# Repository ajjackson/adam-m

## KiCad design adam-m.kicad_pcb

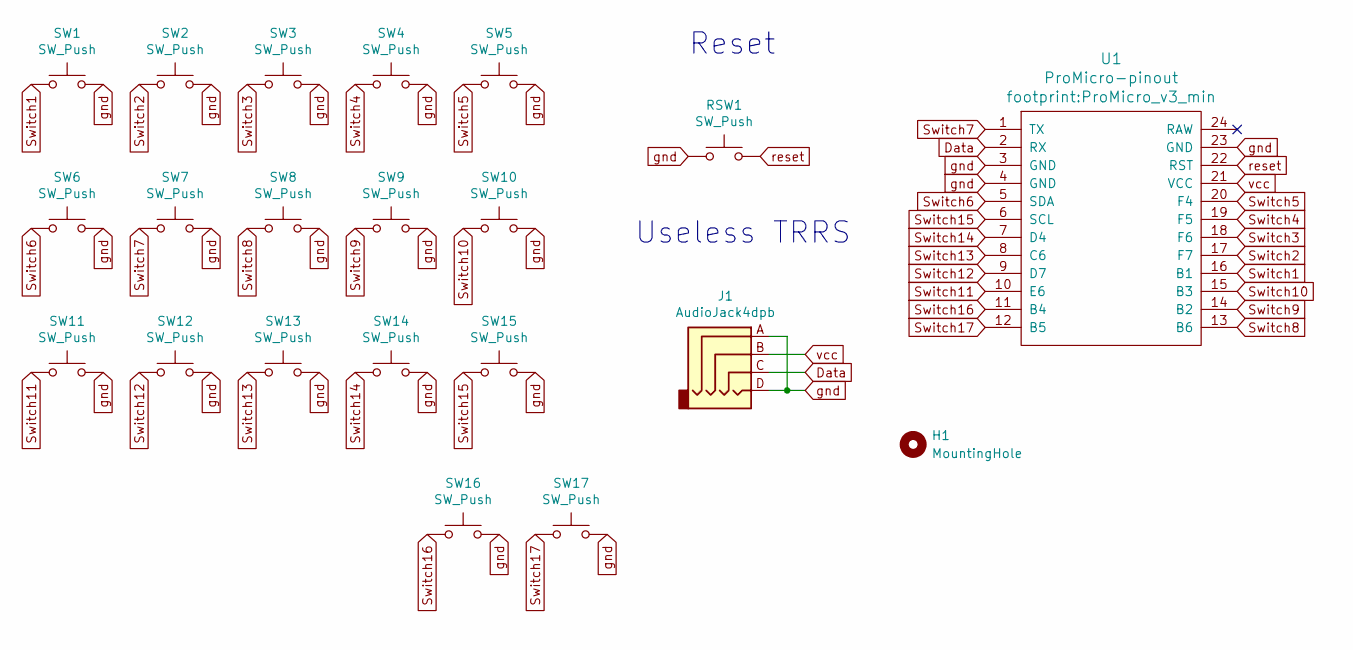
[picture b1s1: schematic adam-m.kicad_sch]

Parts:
H1: MountingHole; Tenting_Puck2
J1: AudioJack4dpb; TRRS-PJ-DPB2
RSW1: SW_Push; ResetSW
SW1, SW2, SW3, SW4, SW5, SW6, SW7, SW8, SW9, SW10, SW11, SW12, SW13, SW14, SW15, SW16, SW17: SW_Push; SW_MX_reversible
U1: ProMicro-pinout; ProMicro_v3_min

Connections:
Data: J1.C, U1.2 (RX)
Switch1: SW1.1, U1.16 (B1)
Switch2: SW2.1, U1.17 (F7)
Switch3: SW3.1, U1.18 (F6)
Switch4: SW4.1, U1.19 (F5)
Switch5: SW5.1, U1.20 (F4)
Switch6: SW6.1, U1.5 (SDA)
Switch7: SW7.1, U1.1 (TX)
Switch8: SW8.1, U1.13 (B6)
Switch9: SW9.1, U1.14 (B2)
Switch10: SW10.1, U1.15 (B3)
Switch11: SW11.1, U1.10 (E6)
Switch12: SW12.1, U1.9 (D7)
Switch13: SW13.1, U1.8 (C6)
Switch14: SW14.1, U1.7 (D4)
Switch15: SW15.1, U1.6 (SCL)
Switch16: SW16.1, U1.11 (B4)
Switch17: SW17.1, U1.12 (B5)
gnd: J1.A, J1.D, RSW1.1, SW1.2, SW2.2, SW3.2, SW4.2, SW5.2, SW6.2, SW7.2, SW8.2, SW9.2, SW10.2, SW11.2, SW12.2, SW13.2, SW14.2, SW15.2, SW16.2, SW17.2, U1.3 (GND), U1.4 (GND), U1.23 (GND)
reset: RSW1.2, U1.22 (RST)
vcc: J1.B, U1.21 (VCC)

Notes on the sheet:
Useless TRRS
Reset

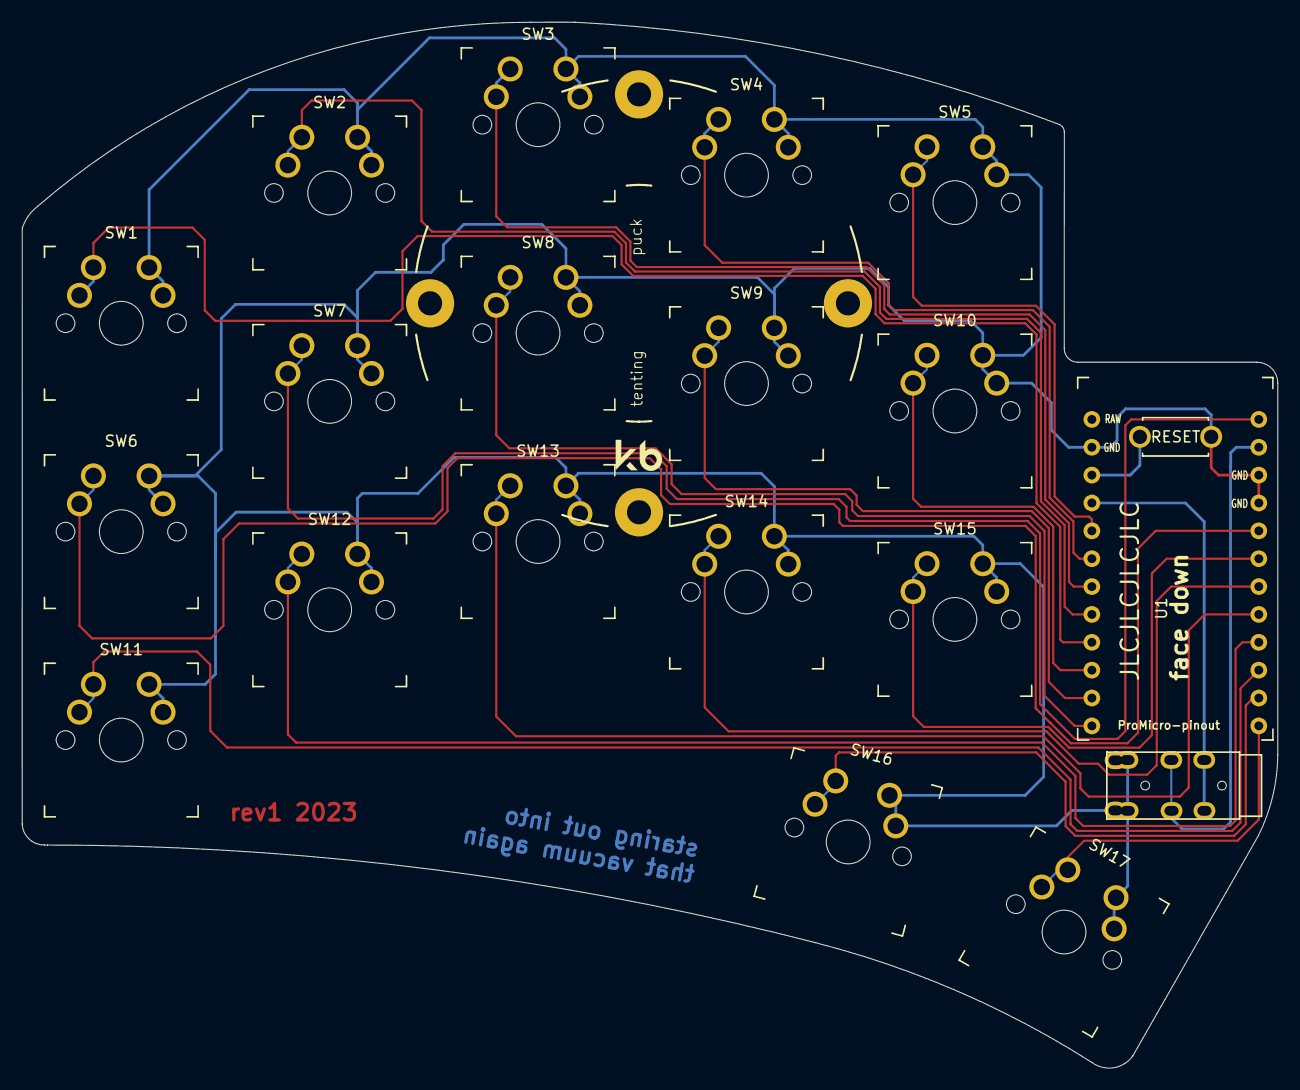
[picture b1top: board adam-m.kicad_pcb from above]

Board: 2 copper layers, 114.5 x 95.3 mm, 21 parts (0 on the bottom side), 21 nets.

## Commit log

2023-06-10 skeleton
2023-06-10 some poc routing
2023-06-10 add gerbers
2023-06-10 fix footprint for mcu
2023-06-11 Tweaks for ERC
    - Removed silkscreen from pads of microcontroller, switch
    - Moved trace closest to board edge to under microcontroller
2023-06-16 more rounding, straighter lines, bit more text
2023-06-18 rebuild gerbers, version-control these uncompressed
2023-06-19 rework switch numbering, rearrange schematic for clarity
2023-06-20 Re-assign TRRS pad labels
    This is a hacked symbol anyway, may as well make it a logical one. Now
    the pad order flows from one end to another of the internal
    connections (note that sleeve connection is at opposite end to pin so
    *appears* out-of-order on PCB footprint). Also explicitly include pads
    that are shorted together by reversible footprint and reflect this in
    schematic.
2023-06-20 Update gerbers; don't VC cache
